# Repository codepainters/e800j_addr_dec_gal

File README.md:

# PROM replacement for Elwro 800 Junior - GAL16V8 variant

Elwro 800 Junior uses two `SN74S474` 512x8 PROMs as IO and memory address decoders. These PROMs are increasingly difficult to obtain (and program), this project provides a `GAL16V8`-based plug-in replacement for both address decoders. 

Note: there is [another version](https://github.com/codepainters/e800j_addr_dec_atf/) using `ATF1502ASL` CPLDs in TQFP-44, if you prefer SMD devices and JTAG programming :) 

Hardware files:

* [pcb](pcb) - schematic/PCB project in KiCAD 8 format
* PDF schematics - [color](pdf/addr_dec_gal.pdf) and [black&white](pdf/addr_dec_gal_bw.pdf)
* [interactive BOM](addr_dec_gal_ibom.html) file (you have to download it and open locally)
* Gerber files (in a [jlcpcb](https://jlcpcb.com/)-compatible ZIP format):
  * [addr\_dec\_gal.zip](gerbers/addr_dec_gal.zip) - single PCB
  * [addr\_dec\_gal\_panel.zip](gerbers/addr_dec_gal_panel.zip) - two PCBs panelized

PLD sources:

* [io](io) - source and JEDEC file for I/O address decoder
* [mem](mem) - source and JEDEC file for memory address decoder

Both decoders have been verified by comparing them against PROM dumps and tested to ensure they function correctly in the Elwro 800 Junior board.

The source files can be compiled with [galasm](https://github.com/daveho/GALasm) like e.g.:

```
$ galasm io.pld
```

Target `GAL16V8` can be programmed with a `.jed` file using `TL866A` or similar programmer.

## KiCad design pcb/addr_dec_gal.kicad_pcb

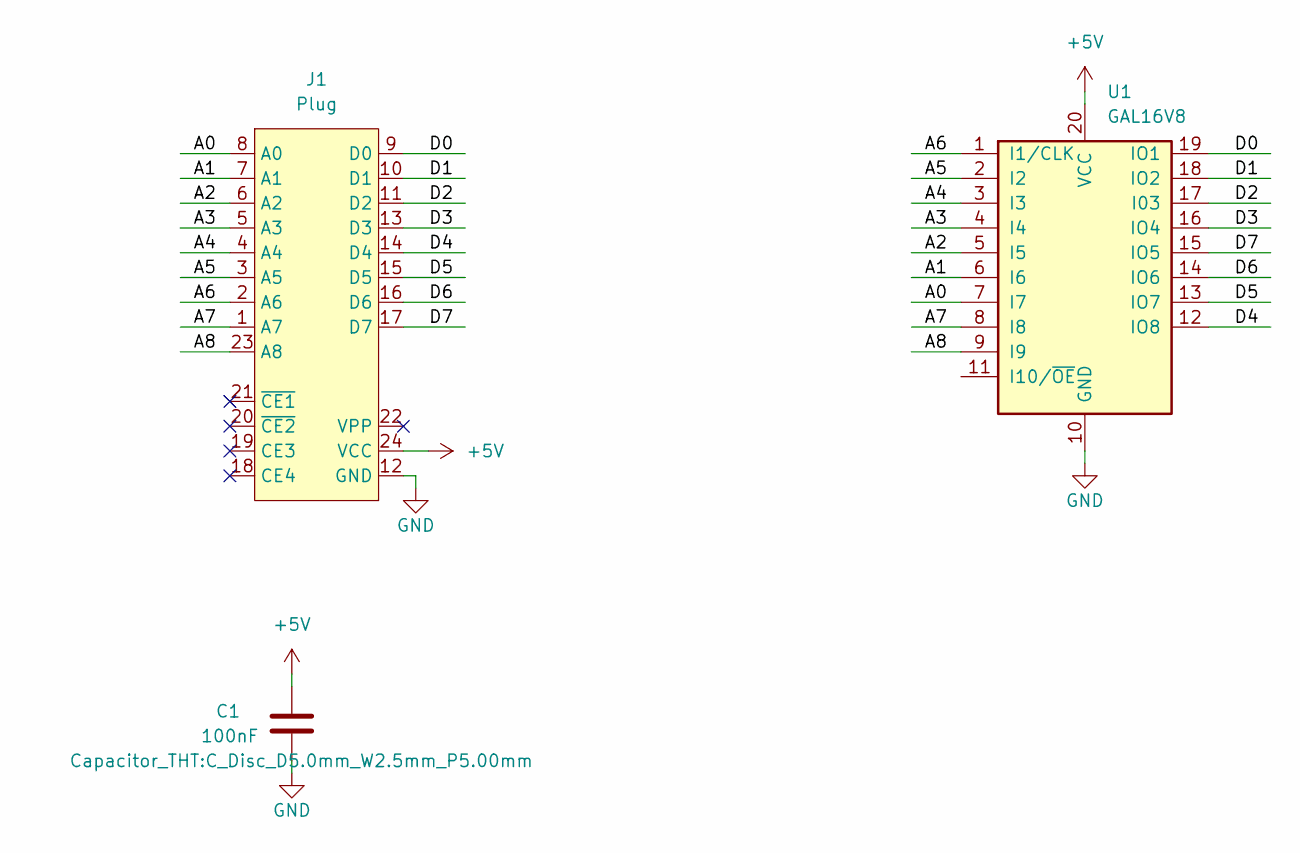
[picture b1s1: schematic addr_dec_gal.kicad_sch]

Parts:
C1: 100nF; C_Disc_D5.0mm_W2.5mm_P5.00mm
J1: Plug; DIP-24_W15.24mm
U1: GAL16V8; DIP-20_W7.62mm

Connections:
+5V: C1.1, J1.24 (VCC), U1.20 (VCC)
/A0: J1.8 (A0), U1.7 (I7)
/A1: J1.7 (A1), U1.6 (I6)
/A2: J1.6 (A2), U1.5 (I5)
/A3: J1.5 (A3), U1.4 (I4)
/A4: J1.4 (A4), U1.3 (I3)
/A5: J1.3 (A5), U1.2 (I2)
/A6: J1.2 (A6), U1.1 (I1/CLK)
/A7: J1.1 (A7), U1.8 (I8)
/A8: J1.23 (A8), U1.9 (I9)
/D0: J1.9 (D0), U1.19 (IO1)
/D1: J1.10 (D1), U1.18 (IO2)
/D2: J1.11 (D2), U1.17 (I03)
/D3: J1.13 (D3), U1.16 (IO4)
/D4: J1.14 (D4), U1.12 (IO8)
/D5: J1.15 (D5), U1.13 (IO7)
/D6: J1.16 (D6), U1.14 (IO6)
/D7: J1.17 (D7), U1.15 (IO5)
GND: C1.2, J1.12 (GND), U1.10 (GND)

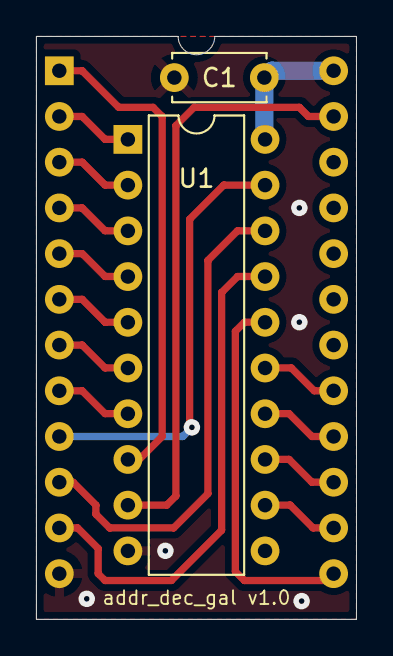
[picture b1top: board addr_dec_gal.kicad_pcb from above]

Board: 2 copper layers, 17.8 x 32.4 mm, 3 parts (0 on the bottom side), 19 nets.

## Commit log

2025-01-22 IO decoder implemented
2025-01-22 MEM decoder implemented
2025-01-22 GAL decoder PCB completed
2025-01-22 README
2025-01-22 Added schematic PDF
2025-01-25 IO: fixed a mistake in nIAL equation
2025-01-25 MEM: not using feedback (can't get it working)
2025-01-25 sch: comsetic
2025-02-10 Image of a real PCB.
2025-02-10 Gerbers / iBOM
2025-02-10 Added panelized gerbers
2025-02-10 README completed
2025-02-10 Update README.md (minor formatting)
2025-02-10 README: minor edit (added a sentece about validation)
2025-02-11 Added schematic PDFs
2025-02-11 Fixed a file name typo
